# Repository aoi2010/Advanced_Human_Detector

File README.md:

# Advanced Human Detector
This is a human detector which uses HmmD Mmwave Sensor to detect humans.

### Inspiration

I wanted to create a human detector using the Mmwave Sensor to detect humans and alert me when human is detected cuz some people always steals the flowers in my garden, and I want to catch them in the act.

### Challenges

Believe it or not, this was my second time using Fusion 360 and KiCad! I watched numerous tutorials and guides and did a kg of googling, but in the end, I'm pretty proud of the final product. I had the most struggle figuring out how to make sketches, and with the new mouse controls, it definitely took me a while to get the hang of it. Also in KiCad, I had a lot of trouble with footprints and making sure everything was aligned properly and the traces were correct(but it became a litle long traces).

### How To Use This
- STEP 1: Buy all the things listed in the BOM, a 0.1µf decoupling capacitor(ceramic & and not mentioned in BOM) & print the case for the sensor and also order the PCB(PCB/motionalr_mcu.zip).
- STEP 2: Solder the 0.1µf decoupling capacitor to the HMMD mmWave Sensor. One leg of it to VCC and another leg to GND.
- STEP 3: Assemble the PCB.
- STEP 4: Flash MicroPython to the XIAO and place the main.py in the XIAO.
- STEP 5: Connect the PCB to the sensor using a LAN Cable(less than 3m) or any twisted Pair Cable(Use the following table as reference).

| Twisted Pair | Use For              |
| ------------ | -------------------- |
| Pair 1       | 3.3V + GND           |
| Pair 2       | TX + GND             |
| Pair 3       | RX + GND             |
| Pair 4       | OT2 + GND            |

- STEP 6: Put the sensor in the case and put it outside or where you want it to be placed.(You may put it near your bedroom so that it alerts you when someone is coming or near your fridge if you have siblings.)
- STEP 7: Put the PCB inside your house while connected to the sensor using a lan cable(length must be less than 3m).
- STEP 8: Power the XIAO using a USB-C Cable.
- STEP 9: Sleep peacefully or If you want to test go near it and see how it screams.
- STEP 10: Do Anything With It.
Thank You! Also Please give a star to this poor fellow if you like the project. Thank You Again!

### Specifications

BOM: 
- 1x [Seeed Studio XIAO ESP32-C3 development board](https://robu.in/product/seeed-studio-xiao-esp32c3-tiny-mcu-board-with-wi-fi-and-ble-battery-charge-supported-power-efficiency-and-rich-interface/)
- 1x [Waveshare HMMD 24 GHz mmWave human presence sensor](https://robu.in/product/waveshare-human-micro-motion-detection-mmwave-sensor-24ghz-mmwave-radar-based-on-s3km1110-adopts-fmcw-technology/)
- 1x [Passive piezo buzzer, 3 V, Ø12 mm](https://robu.in/product/hc12075c-16-cldz-electromagnetic-passive-integrated-buzzer-1-5-3v12x7-5mmimpedance16%CF%89lateralpronunciation/)
- 1x [NPN transistor 2N2222, TO-92 package](https://robu.in/product/2n2222-npn-transistor-pack-of-20/)
- 1x [Resistor 10 kΩ, ¼ W, through-hole](https://robu.in/product/mfr-25frf52-10k-yageo-metal-film-resistors-10k%CF%89-250mw-%C2%B1100ppm-%E2%84%83-%C2%B11-plugind2-4xl6-3mm-through-hole-resistors-rohs/)
- 1x [Resistor 1 kΩ, ¼ W, through-hole](https://robu.in/product/1k-ohm-0-25w-metal-film-resistor-pack-of-100/)
- 1x [Resistor 100–200 Ω, ¼ W, through-hole](https://robu.in/product/0-25w-100-ohm-resistor-pack-of-100/)
- 1x [Resistor 22–33 Ω, through-hole](https://robu.in/product/mf25-33r-multicomp-pro-through-hole-resistor-33-ohm-mf25-series-250-mw-%C2%B1-1-axial-leaded-250-v)
- 1x [Signal diode 1N4148](https://robu.in/product/1n4148-onsemi-100v-1v10ma-4ns-200ma-do-35-switching-diodes-rohs/)
- 2x [0 Ω SMD resistor](https://robu.in/product/1-month-warranty-149/)
- 1x [5-pin connector / header for HMMD sensor - Male](https://robu.in/product/xh-a-2-5mm-5-pin-wafer-male-connector-through-hole-straight/)
- 1x [5-pin connector / header for HMMD sensor - Female](https://robu.in/product/xh-a-aw-2-5mm-5-pin-female-housing-connector-with-300mm-wire28-awg/)
- 1x [LAN / multi-core cable for sensor connection](https://www.amazon.in/Electronic-Spices-Ethernet-Patch-Network/dp/B0D4HYL67Z)
- 4x [M3x16mm Screws](https://onlyscrews.in/products/copy-of-chhd-m3-x-20mm-pack-of-21?variant=48458789257529)
- 4x [M3x4mm Heatset Inserts](https://onlyscrews.in/products/m4-x-4mm-brass-threaded-inserts?variant=49091565650233)
- 1x [PCB](https://www.lioncircuits.com/) 

Others:
- Micropython Firmware
- PCB Gerber File(PCB/motionalr_mcu.zip)
- Case STL files for 3d Printing
- BOM.csv

Schematic            |  PCB         |   Sensor Case (Top)   |   Sensor Case (Bottom)
:-------------------------:|:-------------------------:|:-------------------------:|:-------------------------:|
    |    |  | 

PCB Case (Top)            |  PCB Case (Bottom)
:-------------------------:|:-------------------------:
    |  

### Notes
The code is still basic in functionality because of lack of information on the sensor datasheet, but I will update it as soon as I get the sensor and debug it's output. The case for the mmwave sensor is measured with approx measurement available online, so I will also update the case design once I get the sensor and measure it myself. The PCB will be left bare as I like looking at PCBs.

Edit: I also made the PCB case but after my project was approved. Thank You for understanding.
<div align="center">

## Thanks For Reading! Also leave a star if you like the project! ⭐

</div>

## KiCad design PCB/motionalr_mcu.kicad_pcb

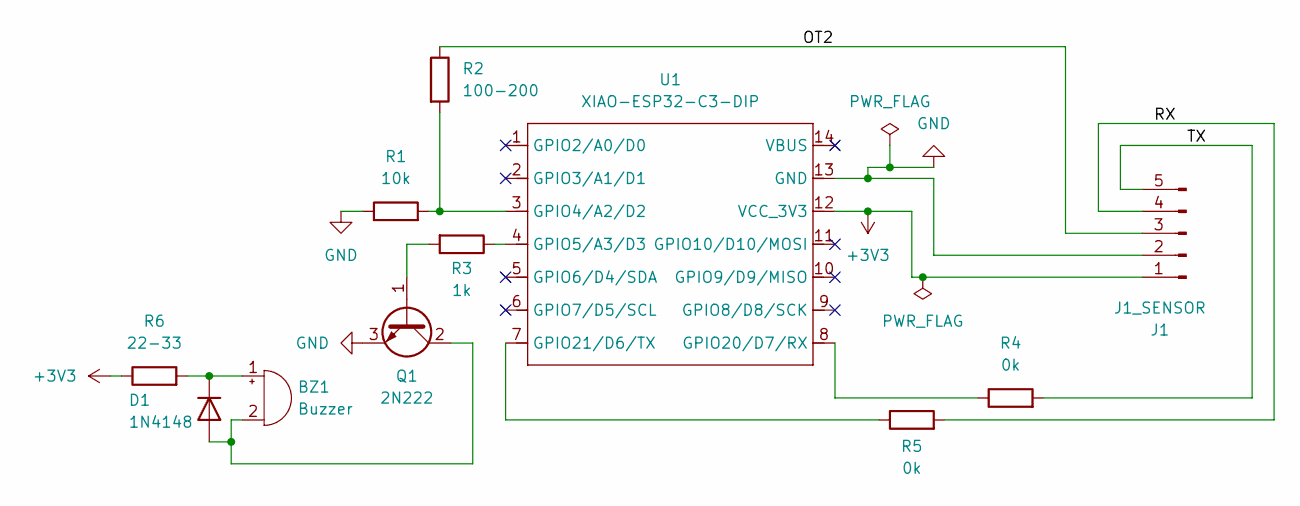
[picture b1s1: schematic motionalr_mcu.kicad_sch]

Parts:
BZ1: Buzzer; Buzzer_12x9.5RM7.6
D1: 1N4148; D_DO-35_SOD27_P7.62mm_Horizontal
J1: J1_SENSOR; JST_XH_B5B-XH-A_1x05_P2.50mm_Vertical
Q1: 2N222; TO-92_HandSolder
R1: 10k; R_Axial_DIN0207_L6.3mm_D2.5mm_P7.62mm_Horizontal
R2: 100-200; R_Axial_DIN0207_L6.3mm_D2.5mm_P7.62mm_Horizontal
R3: 1k; R_Axial_DIN0207_L6.3mm_D2.5mm_P7.62mm_Horizontal
R4, R5: 0k; R_0805_2012Metric_Pad1.20x1.40mm_HandSolder
R6: 22-33; R_Axial_DIN0207_L6.3mm_D2.5mm_P7.62mm_Horizontal
U1: XIAO-ESP32-C3-DIP; XIAO-ESP32C3-DIP

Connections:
+3V3: J1.1, R6.1, U1.12 (VCC_3V3)
/OT2: J1.3, R2.1
/RX: J1.5, R4.2
/TX: J1.4, R5.2
GND: J1.2, Q1.3 (E), R1.1, U1.13 (GND)
unnamed 5: BZ1.1 (+), D1.1 (K), R6.2; also elsewhere on the board
unnamed 6: BZ1.2 (-), D1.2 (A), Q1.2 (C); also elsewhere on the board
unnamed: Q1.1 (B), R3.2
unnamed: R1.2, R2.2, U1.3 (GPIO4/A2/D2)
unnamed: R3.1, U1.4 (GPIO5/A3/D3)
unnamed: R4.1, U1.8 (GPIO20/D7/RX)
unnamed: R5.1, U1.7 (GPIO21/D6/TX)

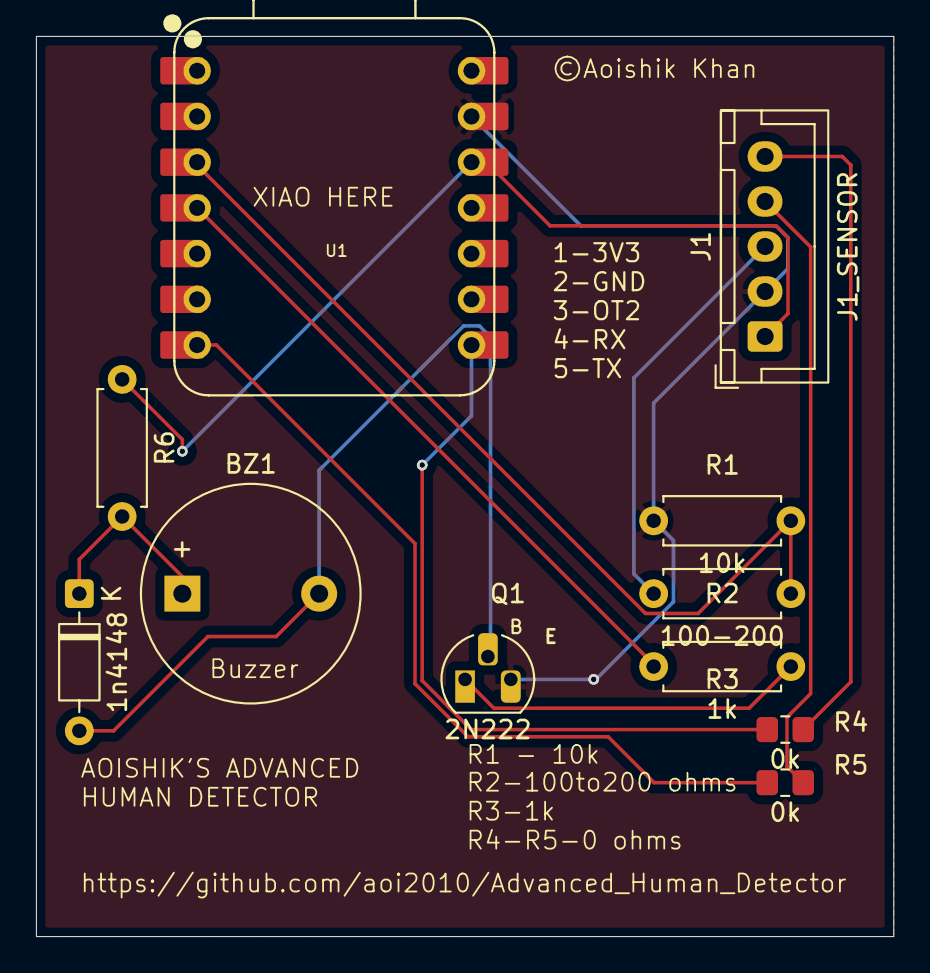
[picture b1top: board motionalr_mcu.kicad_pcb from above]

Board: 2 copper layers, 47.6 x 50.0 mm, 11 parts (0 on the bottom side), 12 nets.

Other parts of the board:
1n4148: 1N4148; D_DO-35_SOD27_P7.62mm_Horizontal

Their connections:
unnamed 5: 1n4148.1 (K); also elsewhere on the board
unnamed 6: 1n4148.2 (A); also elsewhere on the board

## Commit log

2026-02-08 Add sensor CAD models and PCB designs
    Add 3D assets and PCB project for the sensor hardware: 3D-printable STL files (Sensor_top/Bottom), STEP and PNG CAD files for the full case and separated parts, and KiCad PCB project files (motionalr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
2026-02-08 Add Advanced Human Detector MicroPython firmware
    Add Firmware/main.py implementing MicroPython firmware for the Advanced Human Detector project. The script configures an OT2 sensor input and a PWM-driven passive buzzer, includes debounce/confirmati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
2026-02-08 Add PCB layout and schematics images
    Add two new image assets to the PCB folder: PCB/PCB.png (board layout) and PCB/Schematics.png (circuit schematics). These images provide PCB artwork and schematic diagrams for documentation, review, 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
2026-02-09 Add BOM.csv and expand README with project details
    Add a new BOM.csv listing parts, quantities, prices and supplier links. Expand README.md with a project overview, inspiration, challenges, specifications, full BOM summary, asset references (schemati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
2026-02-09 Revise BOM formatting in README.md
    Updated the bill of materials (BOM) section in the README.md to reflect changes in formatting.
2026-02-09 Add links to BOM items in README
    Replace the plain BOM component list with Markdown links to vendor/product pages for each item to make sourcing easier (e.g., Seeed XIAO, Waveshare HMMD, buzzer, resistors, connectors, cables, screws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
2026-02-09 Fix image filename casing in README
    Corrected the filename casing for the bottom sensor case image in the README.
2026-02-09 Fix image filename for sensor case in README
    Corrected the filename for the top sensor case image in the README.
2026-02-10 Changed a typo in schematics
2026-02-18 Add usage instructions to README
    Added a step-by-step guide for using the sensor project, including assembly and connection instructions.
2026-02-20 Add sensor case CAD files
    Add CAD assets for the sensor enclosure: a full case (.f3z) and separate top/bottom models (.f3d). .
2026-03-04 Add PCB case CAD and 3D printing files
    Add CAD assets for the PCB case and printable models: assembled PCB_Case STEP and Autocad (.f3z), preview PNG (CAD/PCB_CASE.png), separate top/bottom STEP and PNG under CAD/Separate, and STL files fo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

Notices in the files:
PCB/motionalr_mcu.kicad_pcb:
©Aoishik Khan
